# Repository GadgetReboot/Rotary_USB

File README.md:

# Rotary_USB
LS30 to MAME Interface<BR><BR>
<br><br><BR><BR>
Uses an ATMega32u4 with a Sparkfun Pro Micro bootloader<br>
to read 1 or 2 rotary joysticks and send out a clockwise or counter-clockwise keystroke when movement occurs.

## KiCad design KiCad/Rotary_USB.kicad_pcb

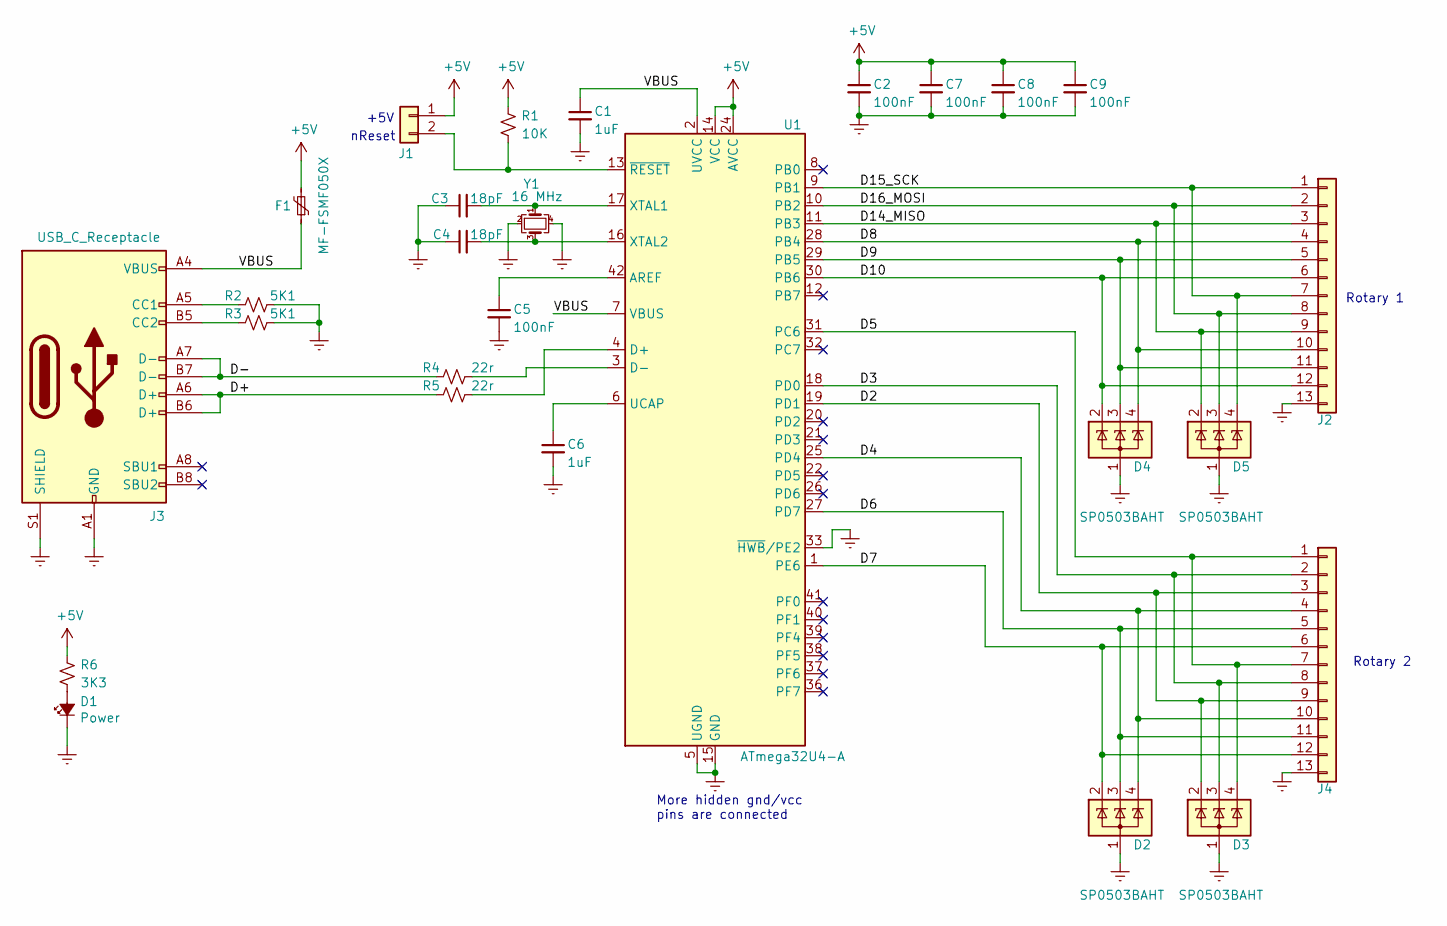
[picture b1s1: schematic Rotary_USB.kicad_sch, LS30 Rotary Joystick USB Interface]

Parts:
C1, C6: 1uF; C_0805_2012Metric
C2, C5, C7, C8, C9: 100nF; C_0805_2012Metric
C3, C4: 18pF; C_0805_2012Metric
D1: Power; LED_0805_2012Metric_Pad1.15x1.40mm_HandSolder
D2, D3, D4, D5: SP0503BAHT; SOT-143
F1: MF-FSMF050X; R_0603_1608Metric_Pad1.05x0.95mm_HandSolder
J1: Conn_01x02; PinHeader_1x02_P2.54mm_Vertical
J2, J4: Conn_01x13; PinHeader_1x13_P2.54mm_Vertical
J3: USB_C_Receptacle; USB_C_Receptacle_XKB_U262-16XN-4BVC11; Part # XKB Connectivity U262-161N-4BVC11
R1: 10K; R_0805_2012Metric_Pad1.20x1.40mm_HandSolder
R2, R3: 5K1; R_0805_2012Metric_Pad1.20x1.40mm_HandSolder
R4, R5: 22r; R_0805_2012Metric_Pad1.20x1.40mm_HandSolder
R6: 3K3; R_0805_2012Metric_Pad1.20x1.40mm_HandSolder
U1: ATmega32U4-A; TQFP-44_10x10mm_P0.8mm
Y1: 16 MHz; Crystal_SMD_Abracon_ABM3B-4Pin_5.0x3.2mm

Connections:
+5V: C2.1, C7.1, C8.1, C9.1, F1.2, J1.1, R1.1, R6.1, U1.14 (VCC), U1.24 (AVCC), U1.34 (VCC), U1.44 (AVCC)
/D2: D3.2 (K), J4.3, J4.9, U1.19 (PD1)
/D3: D3.3 (K), J4.2, J4.8, U1.18 (PD0)
/D4: D2.4 (K), J4.4, J4.10, U1.25 (PD4)
/D5: D3.4 (K), J4.1, J4.7, U1.31 (PC6)
/D6: D2.3 (K), J4.5, J4.11, U1.27 (PD7)
/D7: D2.2 (K), J4.6, J4.12, U1.1 (PE6)
/D8: D4.4 (K), J2.4, J2.10, U1.28 (PB4)
/D9: D4.3 (K), J2.5, J2.11, U1.29 (PB5)
/D10: D4.2 (K), J2.6, J2.12, U1.30 (PB6)
/D14_MISO: D5.2 (K), J2.3, J2.9, U1.11 (PB3)
/D15_SCK: D5.4 (K), J2.1, J2.7, U1.9 (PB1)
/D16_MOSI: D5.3 (K), J2.2, J2.8, U1.10 (PB2)
/D+: J3.A6 (D+), J3.B6 (D+), R5.2
/D-: J3.A7 (D-), J3.B7 (D-), R4.2
/VBUS: C1.1, F1.1, J3.A4 (VBUS), J3.A9 (VBUS), J3.B4 (VBUS), J3.B9 (VBUS), U1.2 (UVCC), U1.7 (VBUS)
GNDREF: C1.2, C2.2, C3.1, C4.1, C5.2, C6.2, C7.2, C8.2, C9.2, D1.1 (K), D2.1 (A), D3.1 (A), D4.1 (A), D5.1 (A), J2.13, J3.A1 (GND), J3.A12 (GND), J3.B1 (GND), J3.B12 (GND), J3.S1 (SHIELD), J4.13, R2.1, R3.1, U1.5 (UGND), U1.15 (GND), U1.23 (GND), U1.33 (~HWB/PE2), U1.35 (GND), U1.43 (GND), Y1.2, Y1.4
unnamed: D1.2 (A), R6.2
unnamed: J1.2, R1.2, U1.13 (~RESET)
unnamed: J3.A5 (CC1), R2.2
unnamed: J3.B5 (CC2), R3.2
unnamed: C5.1, U1.42 (AREF)
unnamed: R5.1, U1.4 (D+)
unnamed: R4.1, U1.3 (D-)
unnamed: C6.1, U1.6 (UCAP)
unnamed: C3.2, U1.17 (XTAL1), Y1.1
unnamed: C4.2, U1.16 (XTAL2), Y1.3

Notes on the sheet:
More hidden gnd/vcc pins are connected
nReset
Rotary 1
+5V
Rotary 2

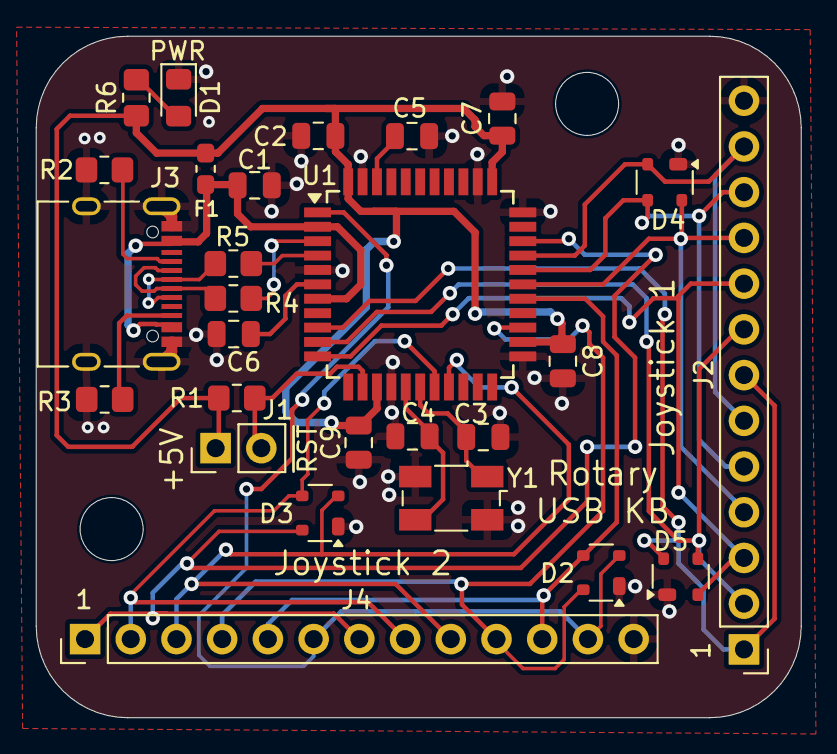
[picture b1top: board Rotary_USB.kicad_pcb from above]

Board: 2 copper layers, 42.5 x 37.9 mm, 27 parts (0 on the bottom side), 27 nets.
